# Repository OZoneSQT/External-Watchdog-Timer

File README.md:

# External-Watchdog-Timer
A PCB in for an external watchdog timer to reset an mcu if it is halted. 

The project is inspired by this project by Ralph Bacon: https://github.com/RalphBacon/194-External-Watchdog-Timer-555-with-PCB 
described in this video: https://www.youtube.com/watch?v=WpihLPvY9Ac&tthat 
that is an modified version of this orginal project: https://www.electronics-lab.com/free-elektor-circuit-ne555-watchdog-timer/ by Wolfgang Borst 

notes: 
      The SO-8 IC's footprint matches NE555 and SI4599 even though an attiny13 has been selected in Eagle
      The 0 ohm resistor R7 is not recommended for battery operation, if not populatet the led will not 
      light on, when the signal is triggered by the countdown in the watchdog timer, to save power
      
      Components are named on the pcb with walues, and can be replaced for another 
      trigger time for the NE555 timer current triggertime are 100mS
      
      Sizes for footprints are 0603, so-8 and sot-23

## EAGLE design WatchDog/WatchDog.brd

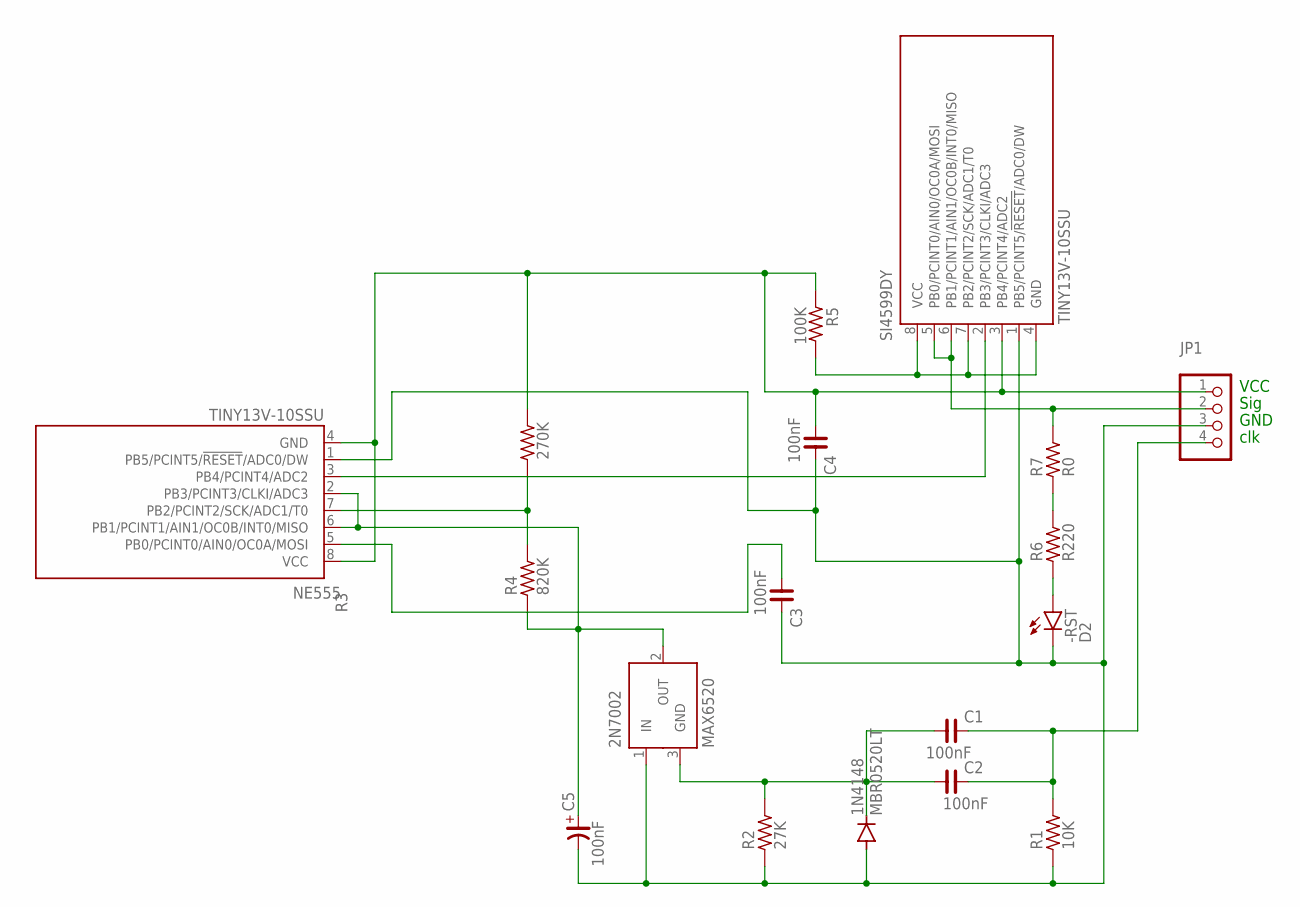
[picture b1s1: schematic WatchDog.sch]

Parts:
1N4148: MBR0520LT; SOD123
2N7002: MAX6520; SOT23
-RST: D2; SML0603
C1, C2, C3, C4: 100nF; C0603
C5: 100nF; CSV-E/F
JP1: PINHD-1X4; 1X04
NE555: TINY13V-10SSU; 8S1
R1: 10K; R0603
R2: 27K; R0603
R3: 270K; R0603
R4: 820K; R0603
R5: 100K; R0603
R6: R220; R0603
R7: R0; R0402
SI4599DY: TINY13V-10SSU; 8S1

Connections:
unnamed: 1N4148.C, 2N7002.3 (GND), C1.1, C2.1, R2.2
unnamed: R6.2, R7.1
unnamed: NE555.7 (PB2/PCINT2/SCK/ADC1/T0), R3.1, R4.2
unnamed: -RST.A, R6.1
unnamed: JP1.2, R7.2, SI4599DY.5 (PB0/PCINT0/AIN0/OC0A/MOSI), SI4599DY.6 (PB1/PCINT1/AIN1/OC0B/INT0/MISO)
unnamed: R5.2, SI4599DY.4 (GND), SI4599DY.7 (PB2/PCINT2/SCK/ADC1/T0), SI4599DY.8 (VCC)
unnamed: 2N7002.2 (OUT), C5.+, NE555.2 (PB3/PCINT3/CLKI/ADC3), NE555.6 (PB1/PCINT1/AIN1/OC0B/INT0/MISO), R4.1
unnamed: C4.1, JP1.1, NE555.4 (GND), NE555.8 (VCC), R3.2, R5.1, SI4599DY.3 (PB4/PCINT4/ADC2)
unnamed: NE555.3 (PB4/PCINT4/ADC2), SI4599DY.2 (PB3/PCINT3/CLKI/ADC3)
unnamed: C3.1, NE555.5 (PB0/PCINT0/AIN0/OC0A/MOSI)
unnamed: C1.2, C2.2, JP1.4, R1.2
unnamed: 1N4148.A, 2N7002.1 (IN), -RST.C, C3.2, C4.2, C5.-, JP1.3, NE555.1 (PB5/PCINT5/!RESET!/ADC0/DW), R1.1, R2.1, SI4599DY.1 (PB5/PCINT5/!RESET!/ADC0/DW)

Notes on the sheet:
VCC
Sig
GND
clk

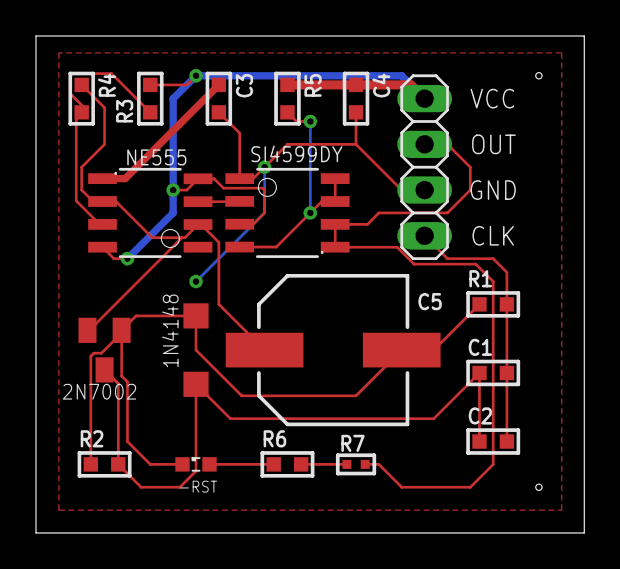
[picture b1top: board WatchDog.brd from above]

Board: 2 copper layers, 30.5 x 27.6 mm, 18 parts (0 on the bottom side), 12 nets.

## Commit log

2020-07-14 Init Eagle and Gerber files

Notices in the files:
parts and their libraries:
rc-master-smd: Copyright (C) 2007, Bob Starr
